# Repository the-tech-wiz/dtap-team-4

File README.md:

# DTAP Team 4

## Getting started

To make it easy for you to get started with GitLab, here's a list of recommended next steps.

Already a pro? Just edit this README.md and make it your own. Want to make it easy? [Use the template at the bottom](#editing-this-readme)!

## Add your files

- [ ] [Create](https://docs.gitlab.com/ee/user/project/repository/web_editor.html#create-a-file) or [upload](https://docs.gitlab.com/ee/user/project/repository/web_editor.html#upload-a-file) files
- [ ] [Add files using the command line](https://docs.gitlab.com/topics/git/add_files/#add-files-to-a-git-repository) or push an existing Git repository with the following command:

```
cd existing_repo
git remote add origin https://version.aalto.fi/gitlab/lel4/dtap-team-4.git
git branch -M main
git push -uf origin main
```

## Integrate with your tools

- [ ] [Set up project integrations](https://version.aalto.fi/gitlab/lel4/dtap-team-4/-/settings/integrations)

## Collaborate with your team

- [ ] [Invite team members and collaborators](https://docs.gitlab.com/ee/user/project/members/)
- [ ] [Create a new merge request](https://docs.gitlab.com/ee/user/project/merge_requests/creating_merge_requests.html)
- [ ] [Automatically close issues from merge requests](https://docs.gitlab.com/ee/user/project/issues/managing_issues.html#closing-issues-automatically)
- [ ] [Enable merge request approvals](https://docs.gitlab.com/ee/user/project/merge_requests/approvals/)
- [ ] [Set auto-merge](https://docs.gitlab.com/user/project/merge_requests/auto_merge/)

## Test and Deploy

Use the built-in continuous integration in GitLab.

- [ ] [Get started with GitLab CI/CD](https://docs.gitlab.com/ee/ci/quick_start/)
- [ ] [Analyze your code for known vulnerabilities with Static Application Security Testing (SAST)](https://docs.gitlab.com/ee/user/application_security/sast/)
- [ ] [Deploy to Kubernetes, Amazon EC2, or Amazon ECS using Auto Deploy](https://docs.gitlab.com/ee/topics/autodevops/requirements.html)
- [ ] [Use pull-based deployments for improved Kubernetes management](https://docs.gitlab.com/ee/user/clusters/agent/)
- [ ] [Set up protected environments](https://docs.gitlab.com/ee/ci/environments/protected_environments.html)

***

# Editing this README

When you're ready to make this README your own, just edit this file and use the handy template below (or feel free to structure it however you want - this is just a starting point!). Thanks to [makeareadme.com](https://www.makeareadme.com/) for this template.

## Suggestions for a good README

Every project is different, so consider which of these sections apply to yours. The sections used in the template are suggestions for most open source projects. Also keep in mind that while a README can be too long and detailed, too long is better than too short. If you think your README is too long, consider utilizing another form of documentation rather than cutting out information.

## Name
Choose a self-explaining name for your project.

## Description
Let people know what your project can do specifically. Provide context and add a link to any reference visitors might be unfamiliar with. A list of Features or a Background subsection can also be added here. If there are alternatives to your project, this is a good place to list differentiating factors.

## Badges
On some READMEs, you may see small images that convey metadata, such as whether or not all the tests are passing for the project. You can use Shields to add some to your README. Many services also have instructions for adding a badge.

## Visuals
Depending on what you are making, it can be a good idea to include screenshots or even a video (you'll frequently see GIFs rather than actual videos). Tools like ttygif can help, but check out Asciinema for a more sophisticated method.

## Installation
Within a particular ecosystem, there may be a common way of installing things, such as using Yarn, NuGet, or Homebrew. However, consider the possibility that whoever is reading your README is a novice and would like more guidance. Listing specific steps helps remove ambiguity and gets people to using your project as quickly as possible. If it only runs in a specific context like a particular programming language version or operating system or has dependencies that have to be installed manually, also add a Requirements subsection.

## Usage
Use examples liberally, and show the expected output if you can. It's helpful to have inline the smallest example of usage that you can demonstrate, while providing links to more sophisticated examples if they are too long to reasonably include in the README.

## Support
Tell people where they can go to for help. It can be any combination of an issue tracker, a chat room, an email address, etc.

## Roadmap
If you have ideas for releases in the future, it is a good idea to list them in the README.

## Contributing
State if you are open to contributions and what your requirements are for accepting them.

For people who want to make changes to your project, it's helpful to have some documentation on how to get started. Perhaps there is a script that they should run or some environment variables that they need to set. Make these steps explicit. These instructions could also be useful to your future self.

You can also document commands to lint the code or run tests. These steps help to ensure high code quality and reduce the likelihood that the changes inadvertently break something. Having instructions for running tests is especially helpful if it requires external setup, such as starting a Selenium server for testing in a browser.

## Authors and acknowledgment
Show your appreciation to those who have contributed to the project.

## License
For open source projects, say how it is licensed.

## Project status
If you have run out of energy or time for your project, put a note at the top of the README saying that development has slowed down or stopped completely. Someone may choose to fork your project or volunteer to step in as a maintainer or owner, allowing your project to keep going. You can also make an explicit request for maintainers.

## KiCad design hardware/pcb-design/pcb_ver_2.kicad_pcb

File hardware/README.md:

# Hardware

Hardware files such as CAD or PCB for DTAP Team 4 project.

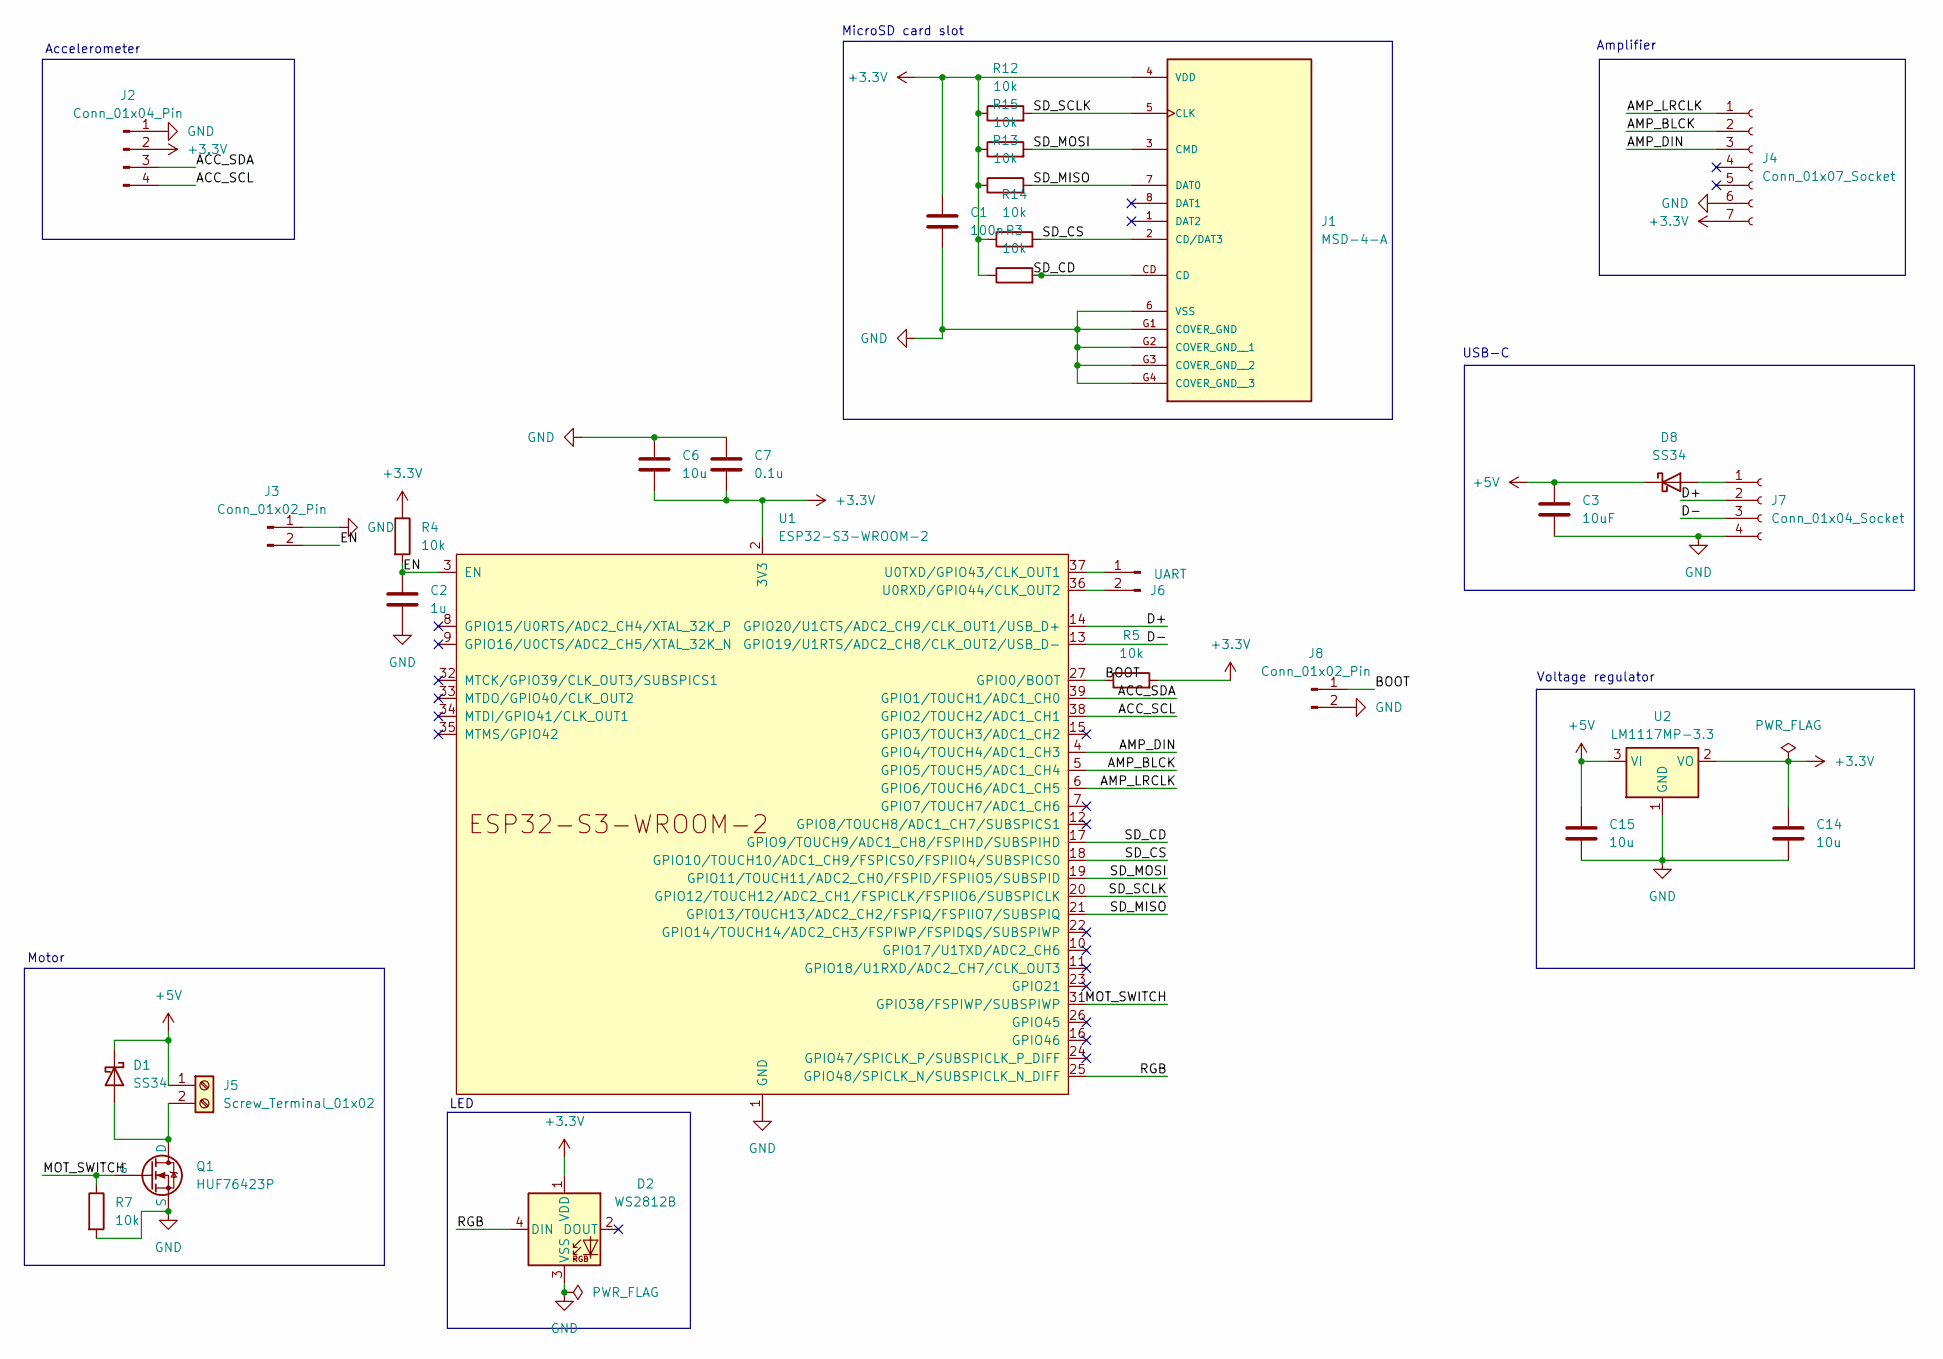
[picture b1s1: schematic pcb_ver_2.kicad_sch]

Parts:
C1: 100n; C_0603_1608Metric_Pad1.08x0.95mm_HandSolder
C2: 1u; C_0603_1608Metric_Pad1.08x0.95mm_HandSolder
C3: 10uF; C_0805_2012Metric_Pad1.18x1.45mm_HandSolder
C6, C14, C15: 10u; C_0805_2012Metric_Pad1.18x1.45mm_HandSolder
C7: 0.1u; C_0603_1608Metric_Pad1.08x0.95mm_HandSolder
D1, D8: SS34; D_SMB-SMC_Universal_Handsoldering
D2: WS2812B; LED_WS2812B_PLCC4_5.0x5.0mm_P3.2mm
J1: MSD-4-A; CUI_MSD-4-A; PARTREV 1.0
J2: Conn_01x04_Pin; NS-Tech_Grove_1x04_P2mm_Vertical
J3, J8: Conn_01x02_Pin; PinSocket_2x01_P2.54mm_Vertical
J4: Conn_01x07_Socket; PinHeader_1x07_P2.54mm_Vertical
J5: Screw_Terminal_01x02; TerminalBlock_RND_205-00012_1x02_P5.00mm_Horizontal
J6: UART; PinHeader_1x02_P2.54mm_Horizontal
J7: Conn_01x04_Socket; NS-Tech_Grove_1x04_P2mm_Vertical
Q1: HUF76423P; TO-220-3_Vertical
R3, R4, R5, R7, R12, R13, R14, R15: 10k; R_0603_1608Metric_Pad0.98x0.95mm_HandSolder
U1: ESP32-S3-WROOM-2
U2: LM1117MP-3.3; SOT-223-3_TabPin2

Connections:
+3.3V: C1.1, C6.2, C7.2, C14.1, D2.1 (VDD), J1.4 (VDD), J2.2, J4.7, R3.1, R4.1, R5.2, R12.1, R13.1, R14.1, R15.1, U1.2 (3V3), U2.2 (VO)
+5V: C3.1, C15.1, D1.1 (K), D8.1 (K), J5.1, U2.3 (VI)
/ACC_SCL: J2.4, U1.38 (GPIO2/TOUCH2/ADC1_CH1)
/ACC_SDA: J2.3, U1.39 (GPIO1/TOUCH1/ADC1_CH0)
/AMP_BLCK: J4.2, U1.5 (GPIO5/TOUCH5/ADC1_CH4)
/AMP_DIN: J4.3, U1.4 (GPIO4/TOUCH4/ADC1_CH3)
/AMP_LRCLK: J4.1, U1.6 (GPIO6/TOUCH6/ADC1_CH5)
/BOOT: J8.1, R5.1, U1.27 (GPIO0/BOOT)
/D+: J7.2, U1.14 (GPIO20/U1CTS/ADC2_CH9/CLK_OUT1/USB_D+)
/D-: J7.3, U1.13 (GPIO19/U1RTS/ADC2_CH8/CLK_OUT2/USB_D-)
/EN: C2.1, J3.2, R4.2, U1.3 (EN)
/MOT_SWITCH: Q1.2 (G), R7.1, U1.31 (GPIO38/FSPIWP/SUBSPIWP)
/RGB: D2.4 (DIN), U1.25 (GPIO48/SPICLK_N/SUBSPICLK_N_DIFF)
/SD_CD: J1.CD, R3.2, U1.17 (GPIO9/TOUCH9/ADC1_CH8/FSPIHD/SUBSPIHD)
/SD_CS: J1.2 (CD/DAT3), R14.2, U1.18 (GPIO10/TOUCH10/ADC1_CH9/FSPICS0/FSPIIO4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)
/SD_MISO: J1.7 (DAT0), R13.2, U1.21 (GPIO13/TOUCH13/ADC2_CH2/FSPIQ/FSPIIO7/S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)
/SD_MOSI: J1.3 (CMD), R15.2, U1.19 (GPIO11/TOUCH11/ADC2_CH0/FSPID/FSPIIO5/S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)
/SD_SCLK: J1.5 (CLK), R12.2, U1.20 (GPIO12/TOUCH12/ADC2_CH1/FSPICLK/FSPIIO6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)
GND: C1.2, C2.2, C3.2, C6.1, C7.1, C14.2, C15.2, D2.3 (VSS), J1.6 (VSS), J1.G1 (COVER_GND), J1.G2 (COVER_GND__1), J1.G3 (COVER_GND__2), J1.G4 (COVER_GND__3), J2.1, J3.1, J4.6, J7.4, J8.2, Q1.3 (S), R7.2, U1.1 (GND), U1.40 (GND), U1.41 (GND), U2.1 (GND)
unnamed: D1.2 (A), J5.2, Q1.1 (D)
unnamed: D8.2 (A), J7.1
unnamed: J6.1, U1.37 (U0TXD/GPIO43/CLK_OUT1)
unnamed: J6.2, U1.36 (U0RXD/GPIO44/CLK_OUT2)

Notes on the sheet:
Voltage regulator
LED
MicroSD card slot
Accelerometer
Motor
USB-C
Amplifier

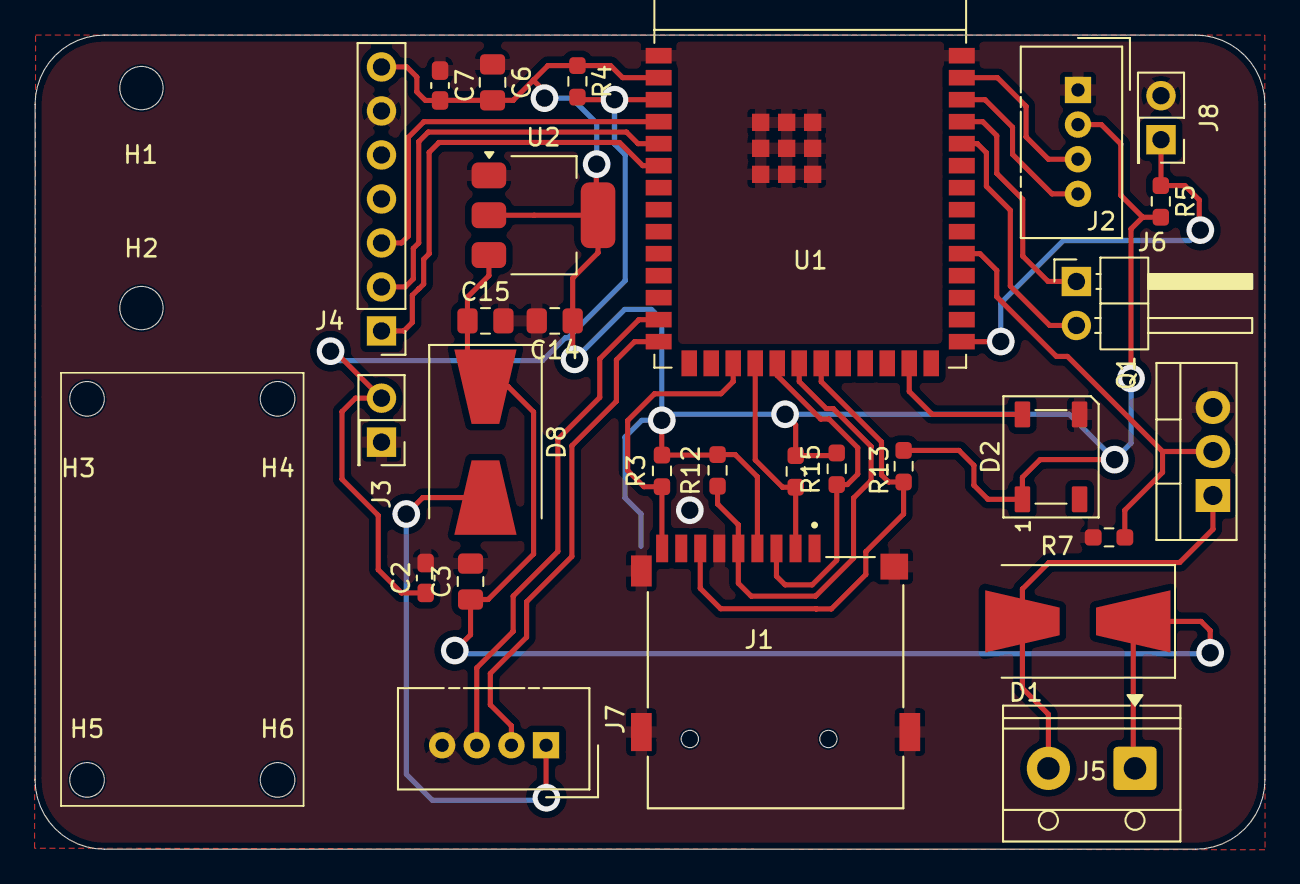
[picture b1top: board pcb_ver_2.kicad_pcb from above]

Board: 2 copper layers, 71.0 x 47.0 mm, 35 parts (1 on the bottom side), 23 nets.

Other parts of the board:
H1, H2: MountingHole_2.5mm
H3, H4, H5, H6: MountingHole_2mm

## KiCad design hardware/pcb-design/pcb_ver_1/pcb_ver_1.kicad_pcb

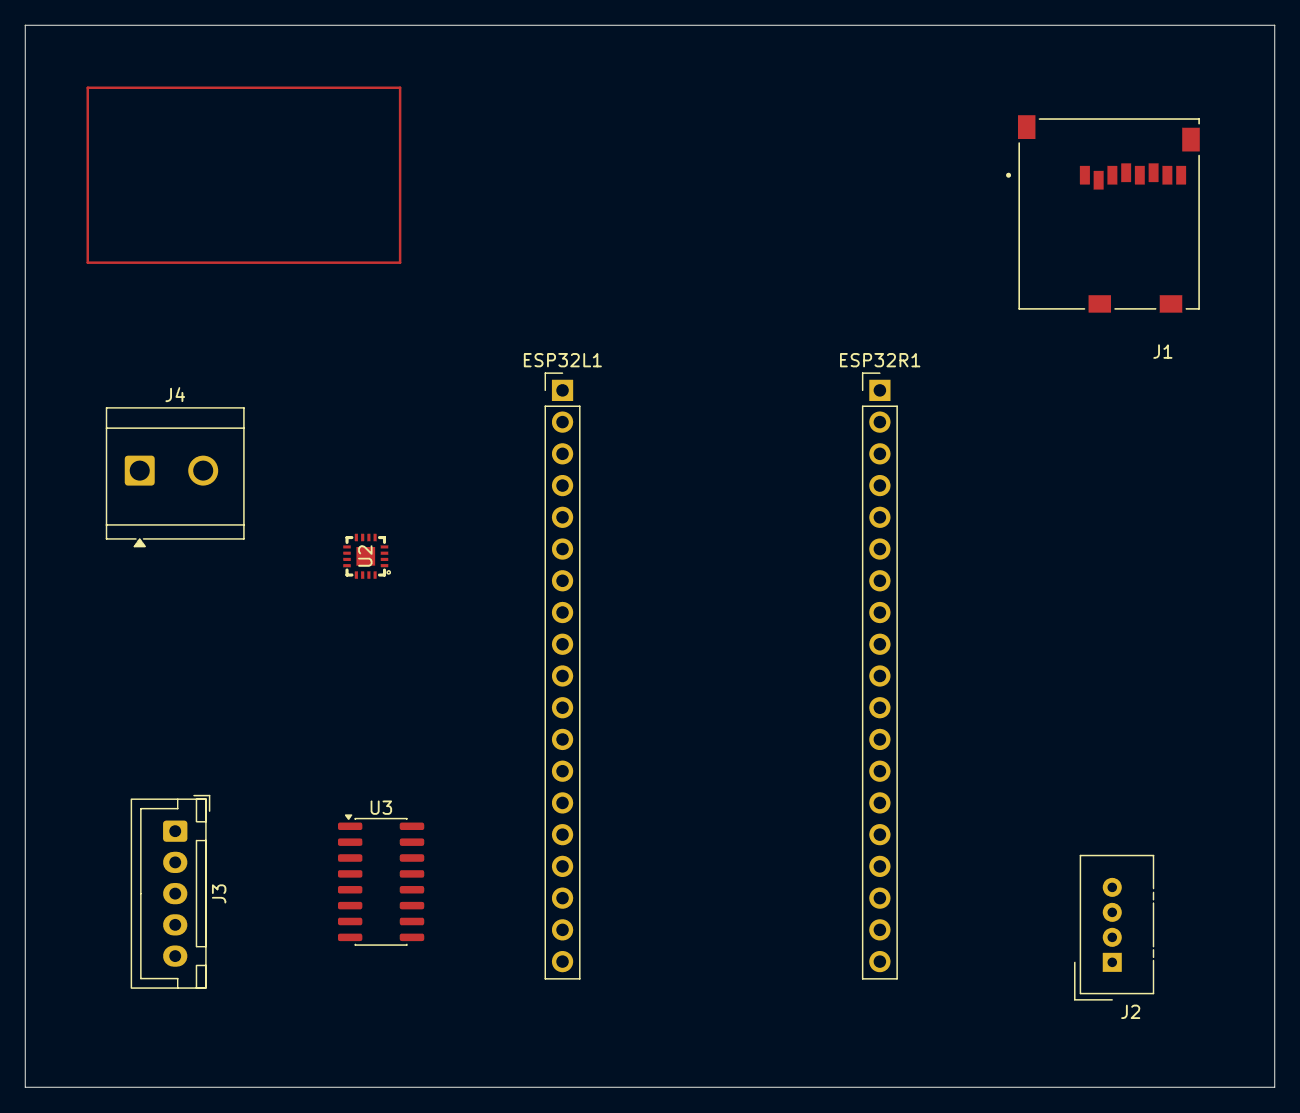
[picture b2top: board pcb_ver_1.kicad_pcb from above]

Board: 2 copper layers, 100.0 x 85.0 mm, 8 parts (0 on the bottom side), 22 nets, no tracks yet.

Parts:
ESP32L1, ESP32R1: Conn_01x19_Pin; PinHeader_1x19_P2.54mm_Vertical
J1: GTFP08441BEU; AMPHENOL_GTFP08441BEU
J2: Conn_01x04_Pin; NS-Tech_Grove_1x04_P2mm_Vertical
J3: Conn_01x05_Pin; JST_XH_B5B-XH-A_1x05_P2.50mm_Vertical
J4: Screw_Terminal_01x02; TerminalBlock_CUI_TB007-508-02_1x02_P5.08mm_Horizontal
U2: MAX98357AETE+T; TQFN-16_L3.0-W3.0-P0.50-BL-EP1.5
U3: ULN2003A; SOIC-16_3.9x9.9mm_P1.27mm

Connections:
+3.3V: ESP32L1.1, J1.4 (VDD), J2.2, U2.7 (VDD)
+5V: ESP32L1.19, J3.1, U3.9 (COM)
/ACC_SCL: ESP32R1.3, J2.4
/ACC_SDA: ESP32R1.4, J2.3
/AMP_BLCK: ESP32L1.9, U2.16 (BCLK)
/AMP_DIN: ESP32L1.8, U2.1 (DIN)
/AMP_LRCLK: ESP32L1.7, U2.14 (LRCLK)
/MOT_IN1: ESP32R1.13, U3.1 (I1)
/MOT_IN2: ESP32R1.15, U3.2 (I2)
/MOT_IN3: ESP32R1.12, U3.3 (I3)
/MOT_IN4: ESP32R1.11, U3.4 (I4)
/SD_CS: ESP32R1.10, J1.2 (CD/DAT3)
/SD_MISO: ESP32R1.8, J1.7 (DAT0)
/SD_MOSI: ESP32R1.2, J1.3 (CMD)
/SD_SCLK: ESP32R1.9, J1.5 (CLK)
GND: ESP32L1.14, ESP32R1.1, ESP32R1.7, J1.6 (VSS), J2.1, U2.15 (GND), U2.17 (EP), U3.8 (GND)
unnamed: J3.2, U3.16 (O1)
unnamed: J3.3, U3.15 (O2)
unnamed: J3.4, U3.14 (O3)
unnamed: J3.5, U3.13 (O4)
unnamed: J4.1, U2.10 (OUTN)
unnamed: J4.2, U2.9 (OUTP)

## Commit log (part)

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2026-01-26 testing both repo pushes
2026-01-26 testing 2
2026-03-18 submodulized
2026-03-18 unsubmoduling, wrong approach
2026-03-18 renamed to firmware
2026-03-18 added hw folder
2026-03-18 implemented git subtrees for multi-repo work
2026-03-26 Initial Backend setup, also added a .gitattributes in order to standardize line endings across operating systems
2026-03-27 Initial frontend commit
2026-04-01 firmware: code for vibrator, piezo sensor
2026-04-01 firmware: copied code to final-firmware arduino project
2026-04-01 renamed device
2026-04-01 firmware: split code into logical chunks
2026-04-03 firmware/final-firmware: fixed incomplete rename
2026-04-03 firmware/final-firmware: edited comment
2026-04-11 Added template REST API documentation in backend/docs/api.md
2026-04-21 firmware: integrate all components
2026-04-21 ignored arduino config
2026-04-21 final-firmware: added restructuring missing last time
2026-04-21 firmware: example code for testing audio functionalities
2026-04-21 final-firmware: finished refactor into .inos
2026-04-21 final-firmware: edited README
2026-04-21 audio: light tweaks
2026-04-21 moved gitignore outside to ignore arduino
2026-04-21 working existing code from firmware
2026-04-21 made previous code work with existing hardware and setup
2026-04-21 hacky fix to reload laugh
2026-04-27 Added a simulator/device.js so we can test the 'device' locally.
2026-04-27 changed device name from 'pelican-1' to 'device-1'
2026-04-27 added volume slider
2026-04-27 slider bugfix
2026-04-28 hardware: pcb version with esp32 devkit
2026-04-30 Connection between frontend code buttons and backend complete! Funcitons currently working: playTrack, stopTrack, setVolume
2026-04-30 removing volume print
2026-05-02 name changes
2026-05-02 clarity changes
2026-05-02 added unconnected page
2026-05-02 very basic unconnected page
2026-05-02 rearranged site
2026-05-04 firmware: mqtt HelloToMyself example complete
2026-05-04 backend: dotenv update
2026-05-05 Added .env.production for frontend build static IP address, locally will use .env with localhost. No changes necessary
2026-05-05 Added frontend deployment script, run on VM to update frontend deployment
2026-05-05 Fixed deployment script ot use full 'npm install' for dependencies
2026-05-05 Added Node Console logging for every API request. Easier debugging
2026-05-05 hardware: clean up folder
2026-05-05 hardware: complete schematic and pcb
2026-05-06 Changeable device name
2026-05-06 Changable device picture
2026-05-06 hardware: change to USB board
2026-05-11 hardware: remove vias and change sizes
2026-05-14 firmware: status send complete
2026-05-14 firmware: command reception and handling done
2026-05-14 media bar dissapears when no track is set
2026-05-14 sylized the dissapearing
2026-05-15 frontend: fixed screen scaling when opening accordion
2026-05-18 frontend: name field auto focuses and saves when clicked away
2026-05-18 frontend: bugfix: pressing the save button while editing puts the user back to editing
2026-05-18 frontend: changed edit text to icon
2026-05-19 firmware: this code works
2026-05-19 frontend: name field look change
2026-05-19 frontend: changed image selector button
2026-05-19 frontend: changed page title
2026-05-19 frontend: name now changes when pressing enter while editing
2026-05-19 frontend: adjusted page for smaller screens
2026-05-19 added repo for fushion, stl, and sliced files
2026-05-19 added body joints excluding ears as stl forms
2026-05-19 firmware: reintegrated pcb version of base non-net code
2026-05-19 firmware: deleted initial-test
2026-05-19 add more body joints w ears as stl, reduce joint length
2026-05-19 add rabbit tail and motor as stl
2026-05-19 Updated the backend api.md to be relevent to current state
2026-05-19 hardware: erm actually renamed
2026-05-19 firmware/final-firmware: light refactor
2026-05-19 firmware/final-firmware: now plays audio continuously (though blocking)
2026-05-19 firmware/final-firmware: enabled failing if sd card not read during setup
2026-05-20 add new component box, integrate it with base, as stl & fusion
2026-05-20 final-firmware: huge rewrite and integration, should in theory work???
2026-05-21 final-firmware: track setting & volume adjustment working
2026-05-21 final-firmware: disable noisy log
2026-05-21 final-firmware: messages now sent only after changes/commands
2026-05-21 final-firmware: added vibration motor debugging
2026-05-21 final-firmware: tweaked volume
2026-05-22 frontend: changed out the accordion for emoji buttons
2026-05-22 frontend: changed button color to make it look softer
2026-05-22 frontend: made the emoji buttons larger
2026-05-22 frontend: centered the device name
2026-05-22 frontend: improved disconnected page
2026-05-22 changed to numeric index IDs
2026-05-22 final-firmware: added demo-sounds
2026-05-22 frontend: updated emojis to match final demo sounds
2026-05-23 final-firmware: disabling stop playing feature (doesnt work and causes bugs)
2026-05-23 final-firmware: tweak threshold to avoid self-trigger
2026-05-23 final-firmware: moved unused stuff around
2026-05-23 final-firmware: fail faster, disabled log
2026-05-23 final-firmware: tweaked shake threshold higher
2026-05-23 final-firmware: reactivating status send timer for keepalive
2026-05-23 final-firmware: 2x volume
2026-05-23 final-firmware: renamed to Cubicle Critter
2026-05-23 final-firmware: added timeout
2026-05-23 final-firmware: fixed timeout & pausing resets esp & fixed delays?
2026-05-23 final-firmware: added initial sound signify done setup
2026-05-23 final-firmware: changed default track
2026-05-23 final-firmware: fixed audio loss & reworked playback and storage
2026-05-23 final-firmware: format
2026-05-23 frontend: rename device
2026-05-25 fist attempt to add frontend status of device rendering
2026-05-25 update base with component box and its bottom lid
2026-05-25 final-firmware: typo
2026-05-25 final-firmware: const float accidentally changed to int causing lack of vol diff
2026-05-31 added license
